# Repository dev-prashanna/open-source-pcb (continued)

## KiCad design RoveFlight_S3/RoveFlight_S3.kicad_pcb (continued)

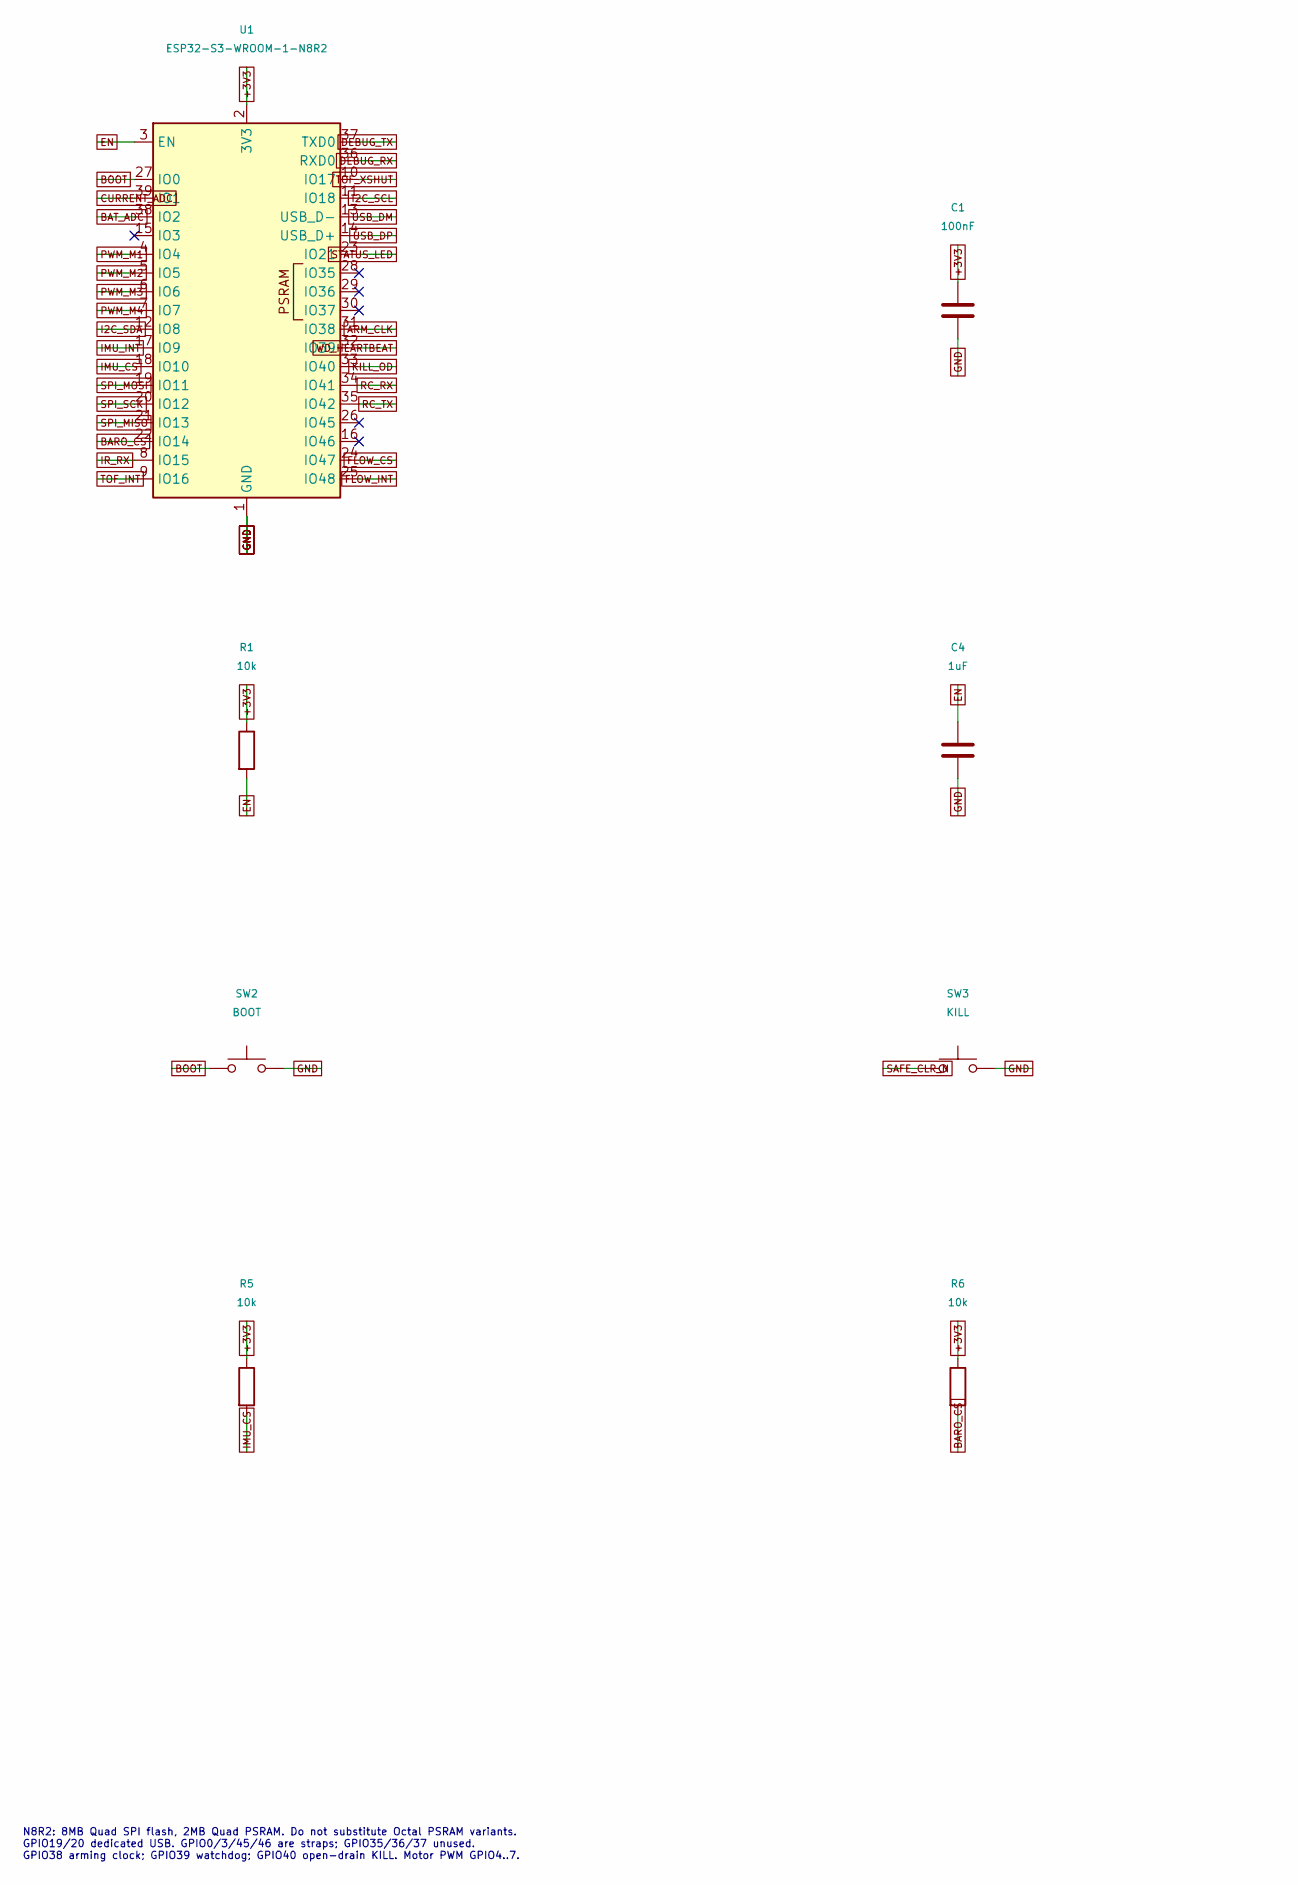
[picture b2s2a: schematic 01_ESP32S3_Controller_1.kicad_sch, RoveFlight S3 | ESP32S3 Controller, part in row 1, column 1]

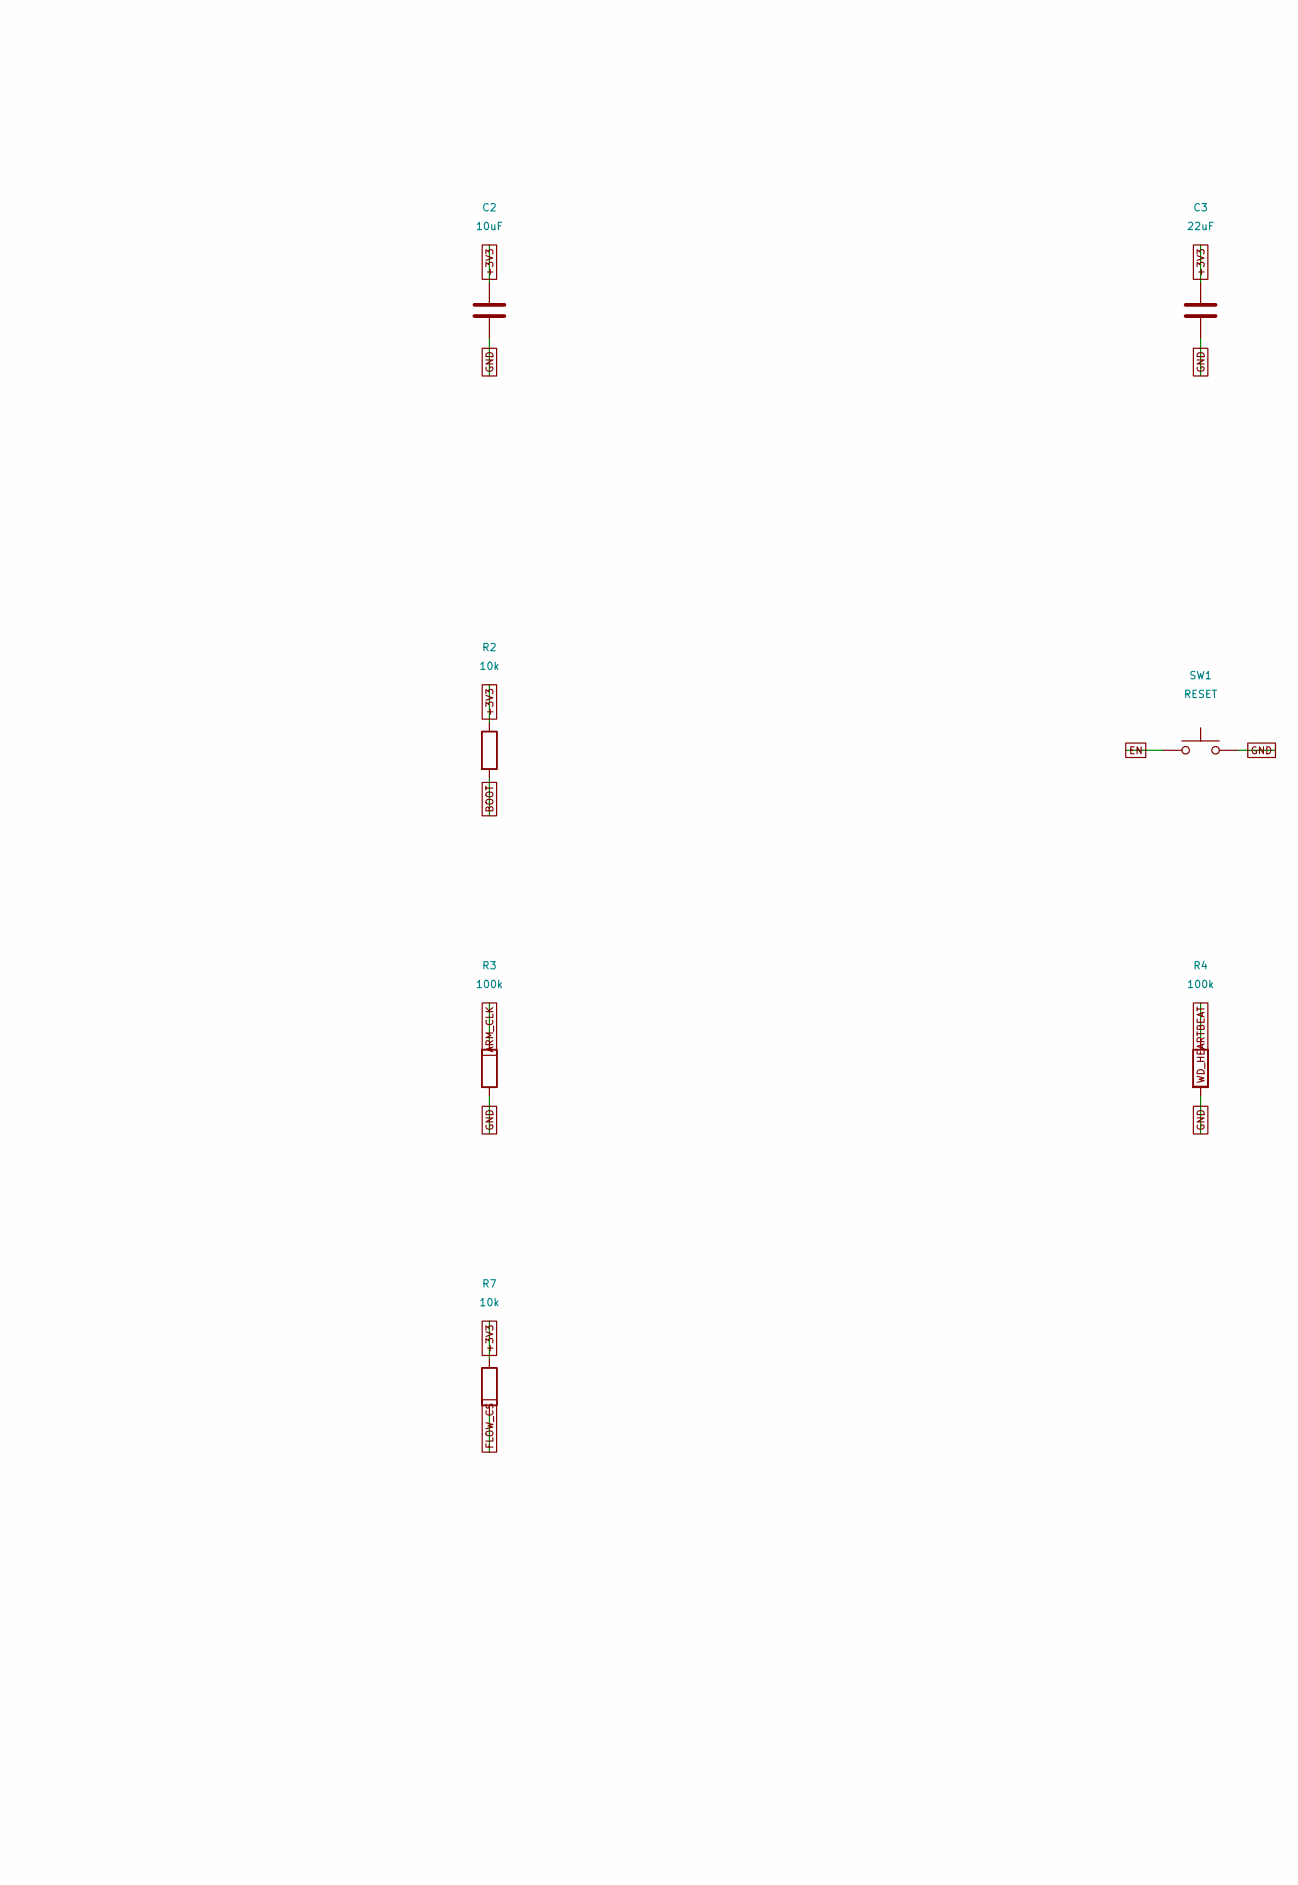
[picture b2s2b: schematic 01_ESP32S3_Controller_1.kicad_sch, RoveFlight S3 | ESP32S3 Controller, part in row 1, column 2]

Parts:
C1: 100nF; C_0402_1005Metric_RF_C1; MPN GRM155R71C104KA88D
C2: 10uF; C_0603_1608Metric; MPN GRM188R60J106ME47D
C3: 22uF; C_0805_2012Metric; MPN GRM21BR60J226ME39L
C4: 1uF; C_0402_1005Metric_RF_C4; MPN GRM155R61A105KE15D
R1: 10k; R_0402_1005Metric_RF_R1; MPN RC0402FR-071002L
R2: 10k; R_0402_1005Metric_RF_R2; MPN RC0402FR-071002L
R3: 100k; R_0402_1005Metric_RF_R3; MPN RC0402FR-071003L
R4: 100k; R_0402_1005Metric_RF_R4; MPN RC0402FR-071003L
R5: 10k; R_0402_1005Metric_RF_R5; MPN RC0402FR-071002L
R6: 10k; R_0402_1005Metric_RF_R6; MPN RC0402FR-071002L
R7: 10k; R_0402_1005Metric_RF_R7; MPN RC0402FR-071002L
SW1: RESET; SW_Push_1P1T-SH_NO_CK_KMR2xxG; MPN KMR221GLFS
SW2: BOOT; SW_Push_1P1T-SH_NO_CK_KMR2xxG; MPN KMR221GLFS
SW3: KILL; SW_Push_1P1T-SH_NO_CK_KMR2xxG; MPN KMR221GLFS
U1: ESP32-S3-WROOM-1-N8R2; ESP32-S3-WROOM-1_Overhang; MPN ESP32-S3-WROOM-1-N8R2

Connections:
+3V3: C1.1, C2.1, C3.1, R1.1, R2.1, R5.1, R6.1, R7.1, U1.2 (3V3); also elsewhere on the board
ARM_CLK: R3.1, U1.31 (IO38); also elsewhere on the board
BARO_CS: R6.2, U1.22 (IO14); also elsewhere on the board
BAT_ADC: U1.38 (IO2); also elsewhere on the board
BOOT: R2.2, SW2.1, U1.27 (IO0); also elsewhere on the board
CURRENT_ADC: U1.39 (IO1); also elsewhere on the board
DEBUG_RX: U1.36 (RXD0); also elsewhere on the board
DEBUG_TX: U1.37 (TXD0); also elsewhere on the board
EN: C4.1, R1.2, SW1.1, U1.3 (EN); also elsewhere on the board
FLOW_CS: R7.2, U1.24 (IO47); also elsewhere on the board
FLOW_INT: U1.25 (IO48); also elsewhere on the board
GND: C1.2, C2.2, C3.2, C4.2, R3.2, R4.2, SW1.2, SW2.2, SW3.2, U1.1 (GND), U1.40 (GND), U1.41 (GND); also elsewhere on the board
I2C_SCL: U1.11 (IO18); also elsewhere on the board
I2C_SDA: U1.12 (IO8); also elsewhere on the board
IMU_CS: R5.2, U1.18 (IO10); also elsewhere on the board
IMU_INT: U1.17 (IO9); also elsewhere on the board
IR_RX: U1.8 (IO15); also elsewhere on the board
KILL_OD: U1.33 (IO40); also elsewhere on the board
PWM_M1: U1.4 (IO4); also elsewhere on the board
PWM_M2: U1.5 (IO5); also elsewhere on the board
PWM_M3: U1.6 (IO6); also elsewhere on the board
PWM_M4: U1.7 (IO7); also elsewhere on the board
RC_RX: U1.34 (IO41); also elsewhere on the board
RC_TX: U1.35 (IO42); also elsewhere on the board
SAFE_CLR_N: SW3.1; also elsewhere on the board
SPI_MISO: U1.21 (IO13); also elsewhere on the board
SPI_MOSI: U1.19 (IO11); also elsewhere on the board
SPI_SCK: U1.20 (IO12); also elsewhere on the board
STATUS_LED: U1.23 (IO21); also elsewhere on the board
TOF_INT: U1.9 (IO16); also elsewhere on the board
TOF_XSHUT: U1.10 (IO17); also elsewhere on the board
USB_DM: U1.13 (USB_D-); also elsewhere on the board
USB_DP: U1.14 (USB_D+); also elsewhere on the board
WD_HEARTBEAT: R4.1, U1.32 (IO39); also elsewhere on the board

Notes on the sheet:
N8R2: 8MB Quad SPI flash, 2MB Quad PSRAM. Do not substitute Octal PSRAM variants. GPIO19/20 dedicated USB. GPIO0/3/45/46 are straps; GPIO35/36/37 unused. GPIO38 arming clock; GPIO39 watchdog; GPIO40 open-drain KILL. Motor PWM GPIO4..7.

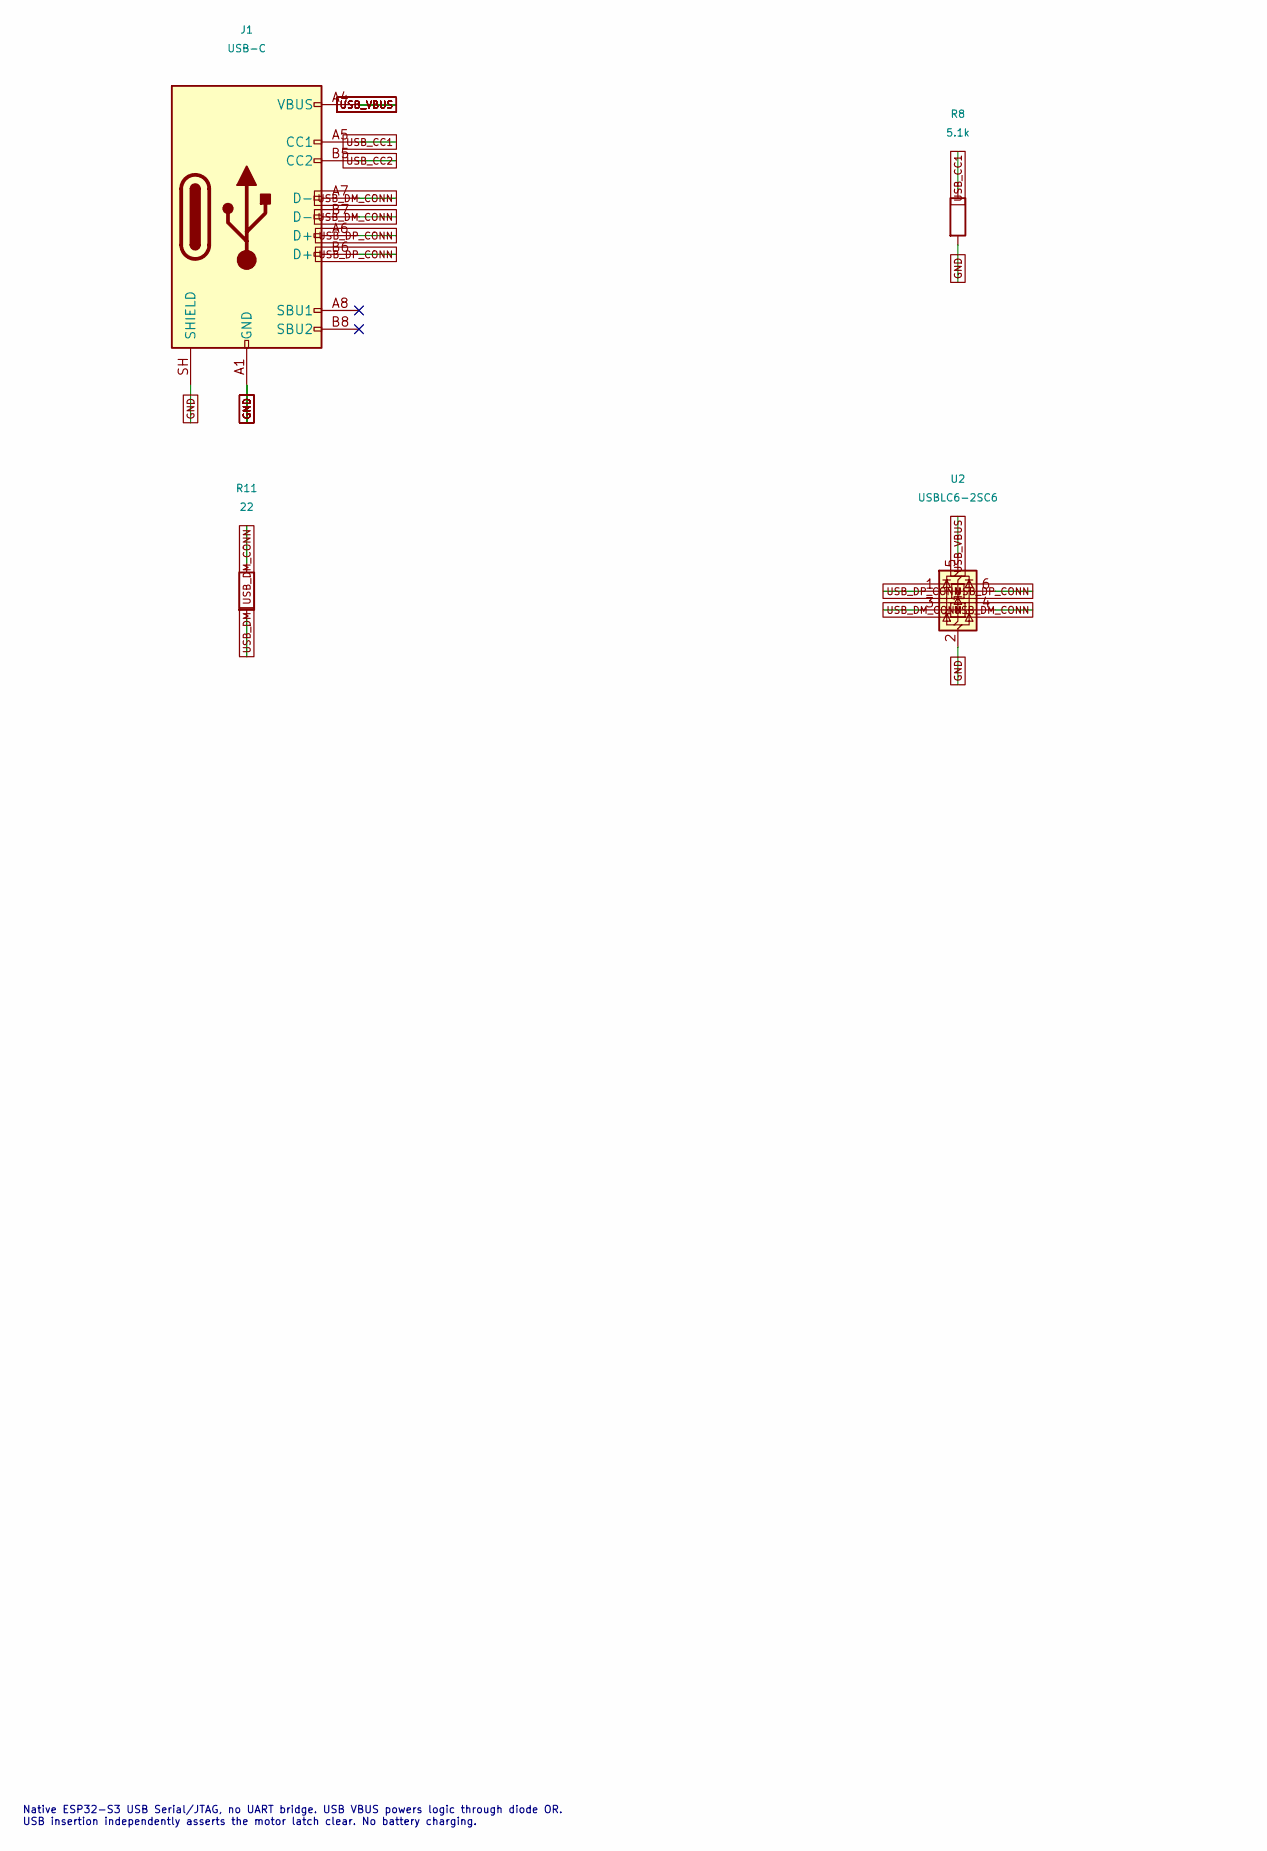
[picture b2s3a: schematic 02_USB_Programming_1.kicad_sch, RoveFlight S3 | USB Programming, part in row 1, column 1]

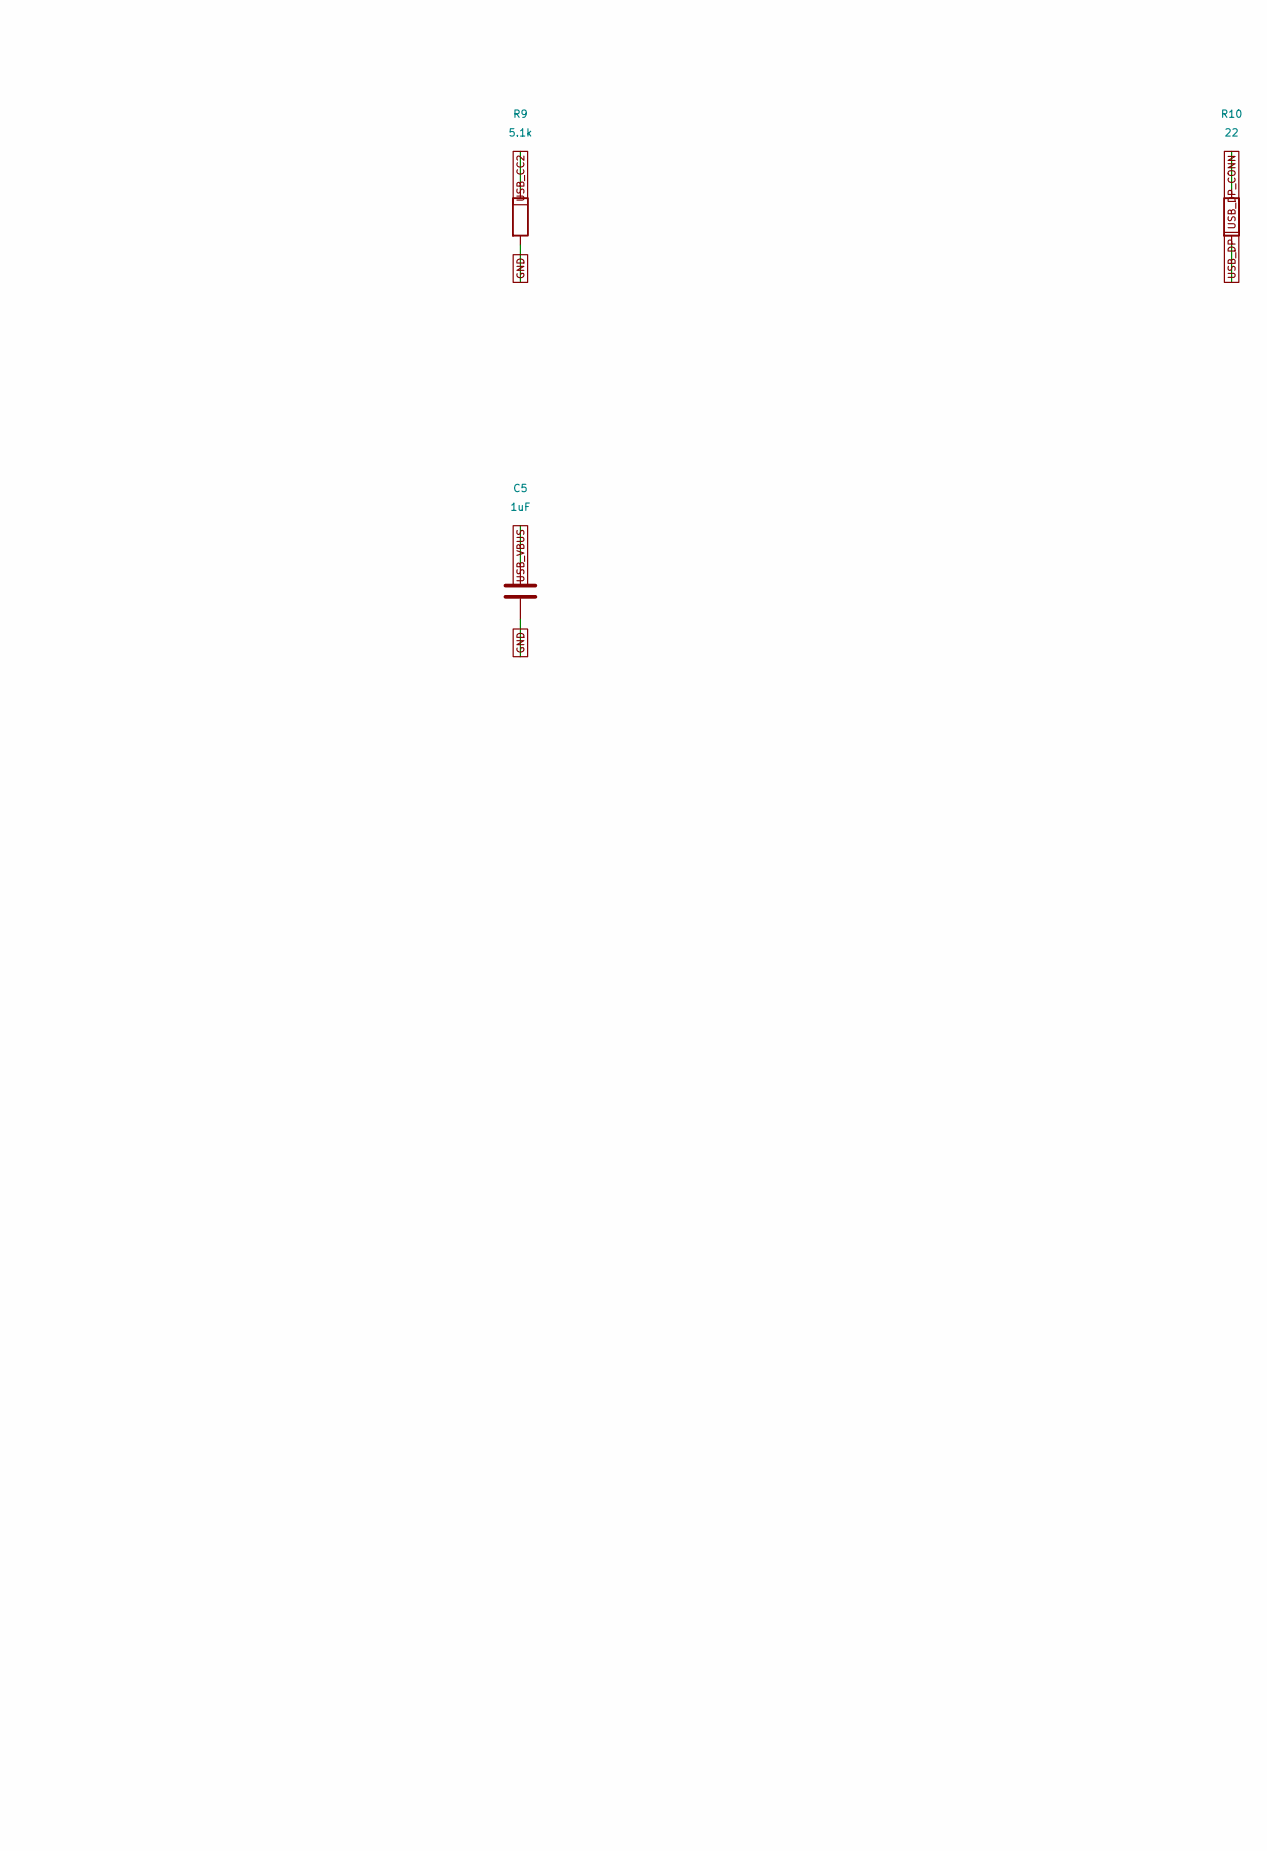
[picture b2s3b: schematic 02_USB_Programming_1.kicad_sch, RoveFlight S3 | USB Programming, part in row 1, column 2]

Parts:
C5: 1uF; C_0402_1005Metric_RF_C5; MPN GRM155R61A105KE15D
J1: USB-C; USB_C_Receptacle_HRO_TYPE-C-31-M-12; MPN TYPE-C-31-M-12
R8: 5.1k; R_0402_1005Metric_RF_R8; MPN RC0402FR-075101L
R9: 5.1k; R_0402_1005Metric_RF_R9; MPN RC0402FR-075101L
R10: 22; R_0402_1005Metric_RF_R10; MPN RC0402FR-0722R0L
R11: 22; R_0402_1005Metric_RF_R11; MPN RC0402FR-0722R0L
U2: USBLC6-2SC6; SOT-23-6; MPN USBLC6-2SC6

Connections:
GND: C5.2, J1.A1 (GND), J1.A12 (GND), J1.B1 (GND), J1.B12 (GND), J1.SH (SHIELD), R8.2, R9.2, U2.2 (GND); also elsewhere on the board
USB_CC1: J1.A5 (CC1), R8.1
USB_CC2: J1.B5 (CC2), R9.1
USB_DM: R11.2; also elsewhere on the board
USB_DM_CONN: J1.A7 (D-), J1.B7 (D-), R11.1, U2.3 (I/O2), U2.4 (I/O2)
USB_DP: R10.2; also elsewhere on the board
USB_DP_CONN: J1.A6 (D+), J1.B6 (D+), R10.1, U2.1 (I/O1), U2.6 (I/O1)
USB_VBUS: C5.1, J1.A4 (VBUS), J1.A9 (VBUS), J1.B4 (VBUS), J1.B9 (VBUS), U2.5 (VBUS); also elsewhere on the board

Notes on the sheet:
Native ESP32-S3 USB Serial/JTAG, no UART bridge. USB VBUS powers logic through diode OR. USB insertion independently asserts the motor latch clear. No battery charging.

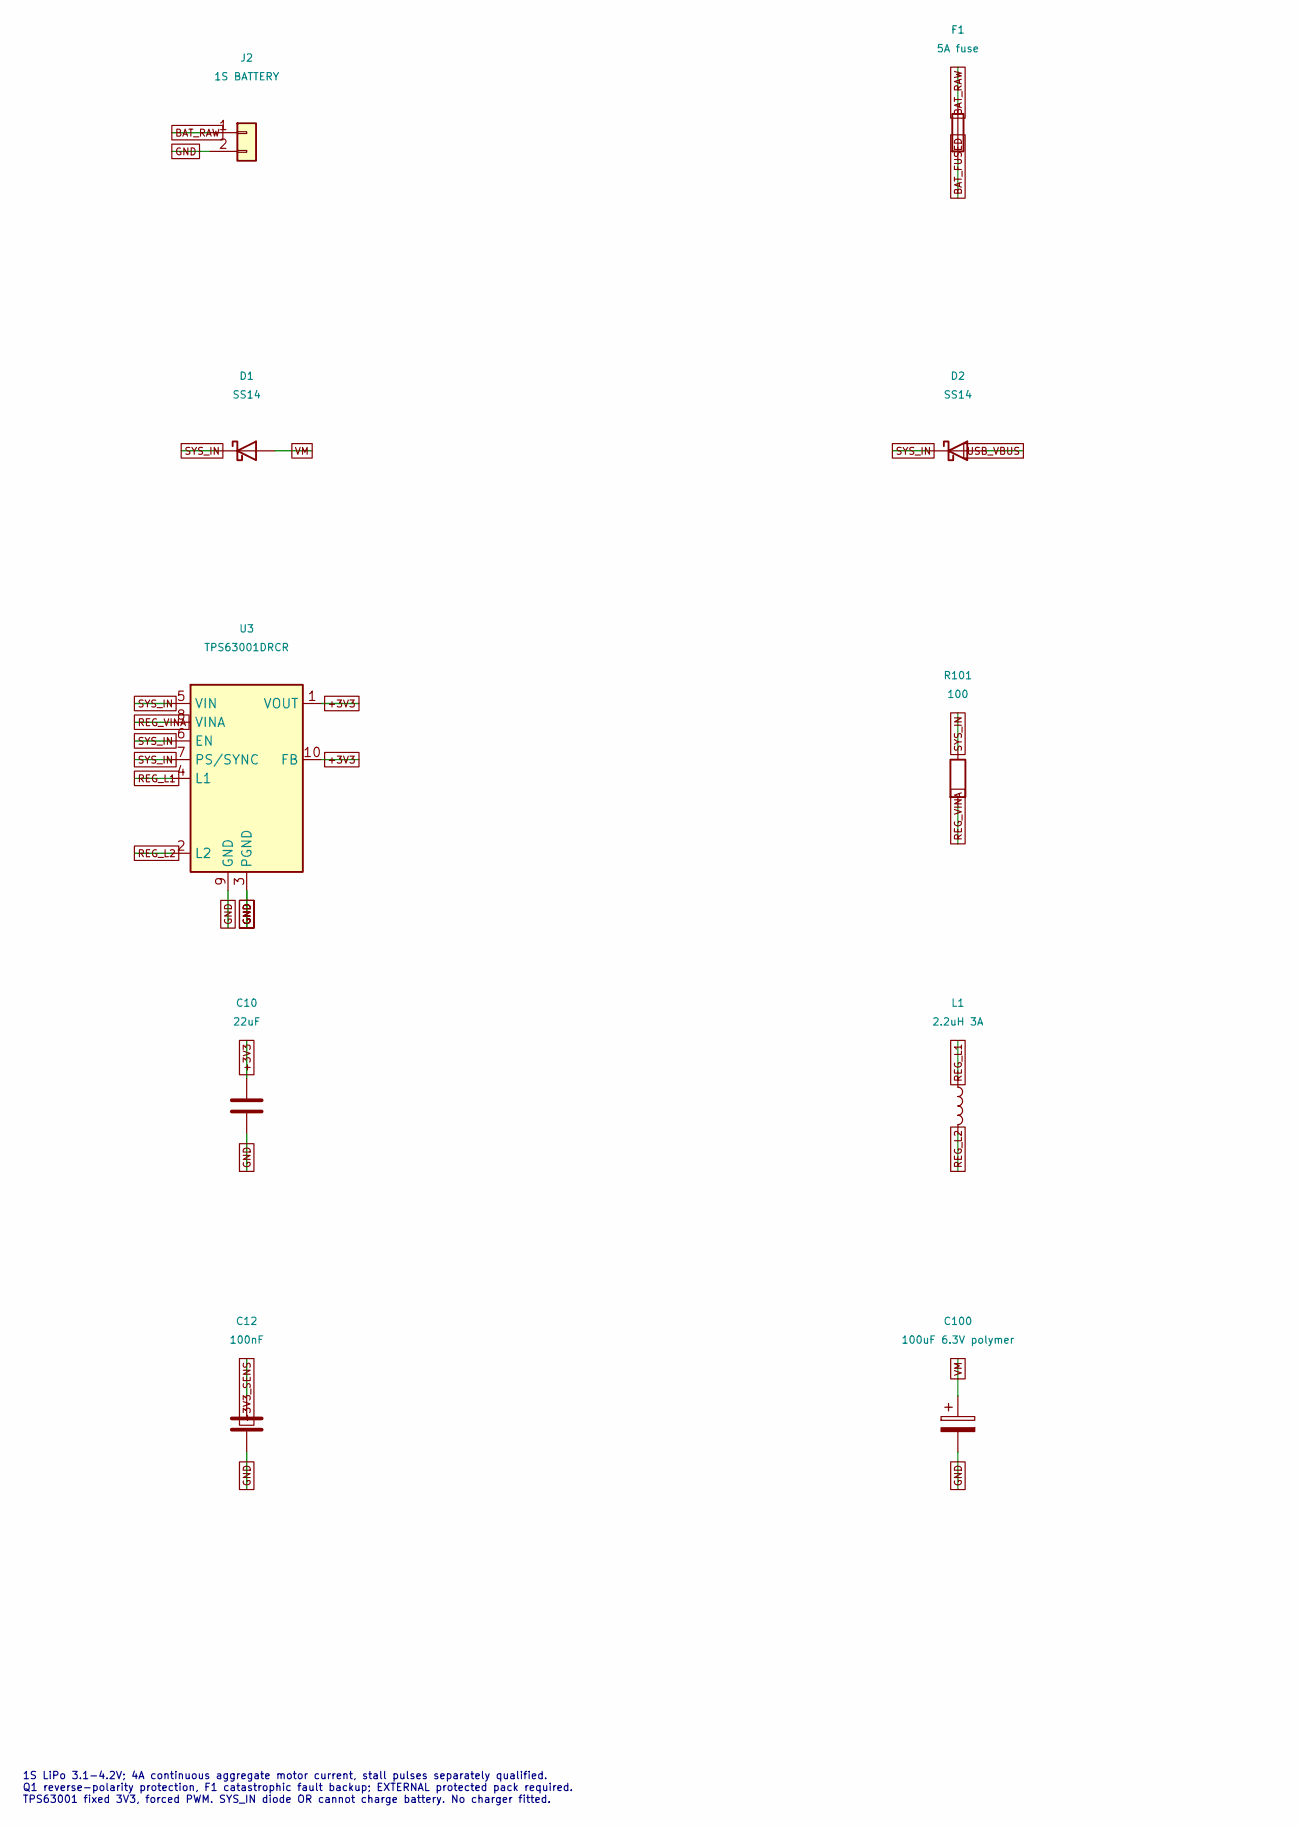
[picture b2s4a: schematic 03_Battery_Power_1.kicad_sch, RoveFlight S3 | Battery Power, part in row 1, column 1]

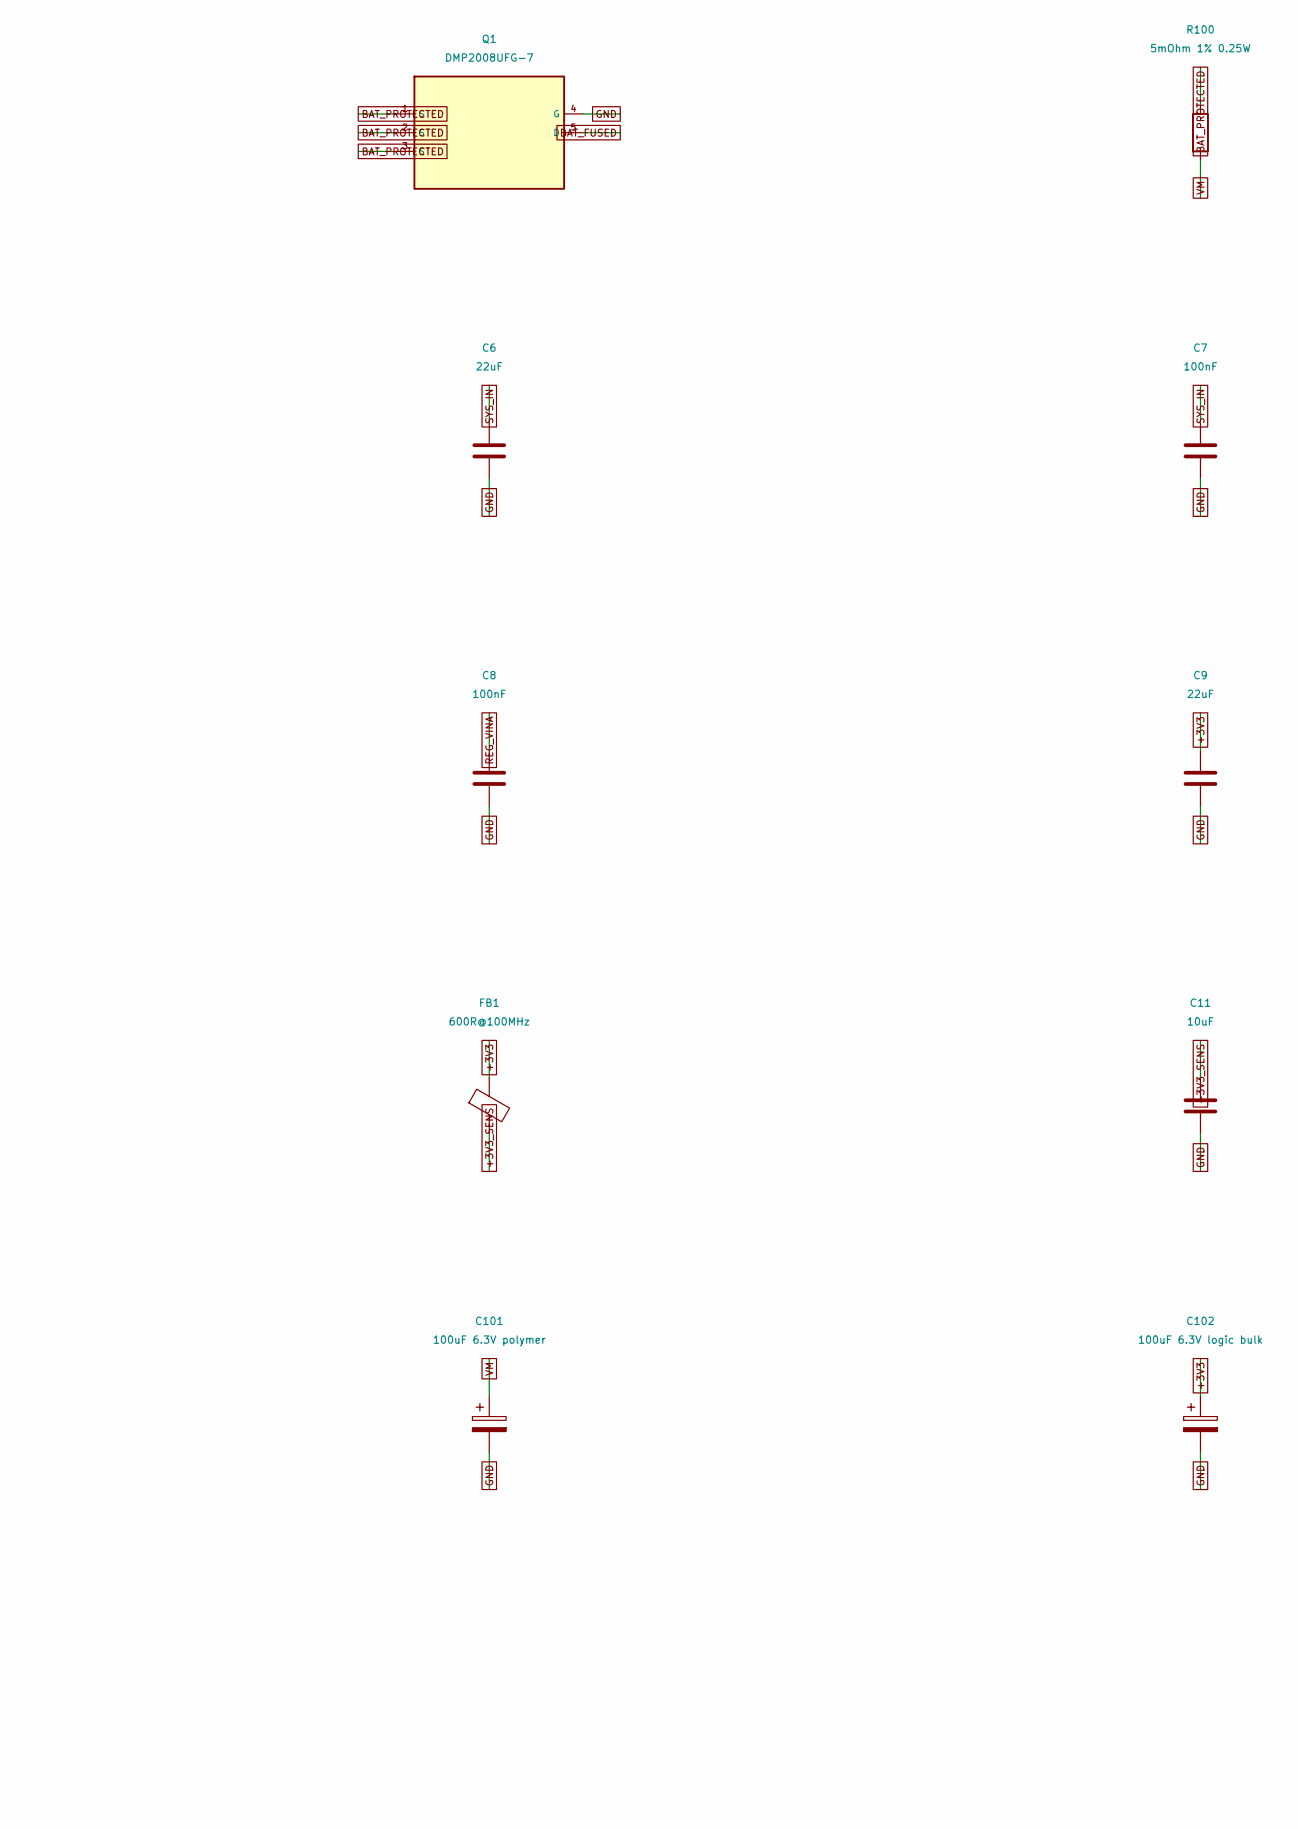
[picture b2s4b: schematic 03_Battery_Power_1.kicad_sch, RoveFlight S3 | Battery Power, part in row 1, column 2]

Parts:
C6, C9, C10: 22uF; C_0805_2012Metric; MPN GRM21BR60J226ME39L
C7: 100nF; C_0402_1005Metric_RF_C7; MPN GRM155R71C104KA88D
C8: 100nF; C_0402_1005Metric_RF_C8; MPN GRM155R71C104KA88D
C11: 10uF; C_0603_1608Metric; MPN GRM188R60J106ME47D
C12: 100nF; C_0402_1005Metric_RF_C12; MPN GRM155R71C104KA88D
C100, C101: 100uF 6.3V polymer; CP_EIA-3528-21_Kemet-B; MPN T520B107M006ATE070
C102: 100uF 6.3V logic bulk; CP_EIA-3528-21_Kemet-B; MPN T520B107M006ATE070
D1, D2: SS14; D_SMA; MPN SS14-13-F
F1: 5A fuse; Fuse_1206_3216Metric; MPN 0467005.NR
FB1: 600R@100MHz; L_0603_1608Metric; MPN BLM18AG601SN1D
J2: 1S BATTERY; BatteryPads; MPN PCB_SOLDER_PADS_20AWG
L1: 2.2uH 3A; L_Vishay_IFSC-1515AH_4x4x1.8mm; MPN IFSC1515AHER2R2M01
Q1: DMP2008UFG-7; Diodes_PowerDI3333-8; MPN DMP2008UFG-7
R100: 5mOhm 1% 0.25W; R_1206_3216Metric; MPN WSL1206R0050FEA
R101: 100; R_0402_1005Metric_RF_R101; MPN RC0402FR-071000L
U3: TPS63001DRCR; Texas_DRC0010J_ThermalVias_RF_U3; MPN TPS63001DRCR

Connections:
+3V3: C9.1, C10.1, C102.1, FB1.1, U3.1 (VOUT), U3.10 (FB); also elsewhere on the board
+3V3_SENS: C11.1, C12.1, FB1.2; also elsewhere on the board
BAT_FUSED: F1.2, Q1.5 (D)
BAT_PROTECTED: Q1.1 (S), Q1.2 (S), Q1.3 (S), R100.1; also elsewhere on the board
BAT_RAW: F1.1, J2.1
GND: C6.2, C7.2, C8.2, C9.2, C10.2, C11.2, C12.2, C100.2, C101.2, C102.2, J2.2, Q1.4 (G), U3.3 (PGND), U3.9 (GND), U3.11 (PGND); also elsewhere on the board
REG_L1: L1.1, U3.4 (L1)
REG_L2: L1.2, U3.2 (L2)
REG_VINA: C8.1, R101.2, U3.8 (VINA)
SYS_IN: C6.1, C7.1, D1.1 (K), D2.1 (K), R101.1, U3.5 (VIN), U3.6 (EN), U3.7 (PS/SYNC)
USB_VBUS: D2.2 (A); also elsewhere on the board
VM: C100.1, C101.1, D1.2 (A), R100.2; also elsewhere on the board

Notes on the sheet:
1S LiPo 3.1-4.2V; 4A continuous aggregate motor current, stall pulses separately qualified. Q1 reverse-polarity protection, F1 catastrophic fault backup; EXTERNAL protected pack required. TPS63001 fixed 3V3, forced PWM. SYS_IN diode OR cannot charge battery. No charger fitted.
